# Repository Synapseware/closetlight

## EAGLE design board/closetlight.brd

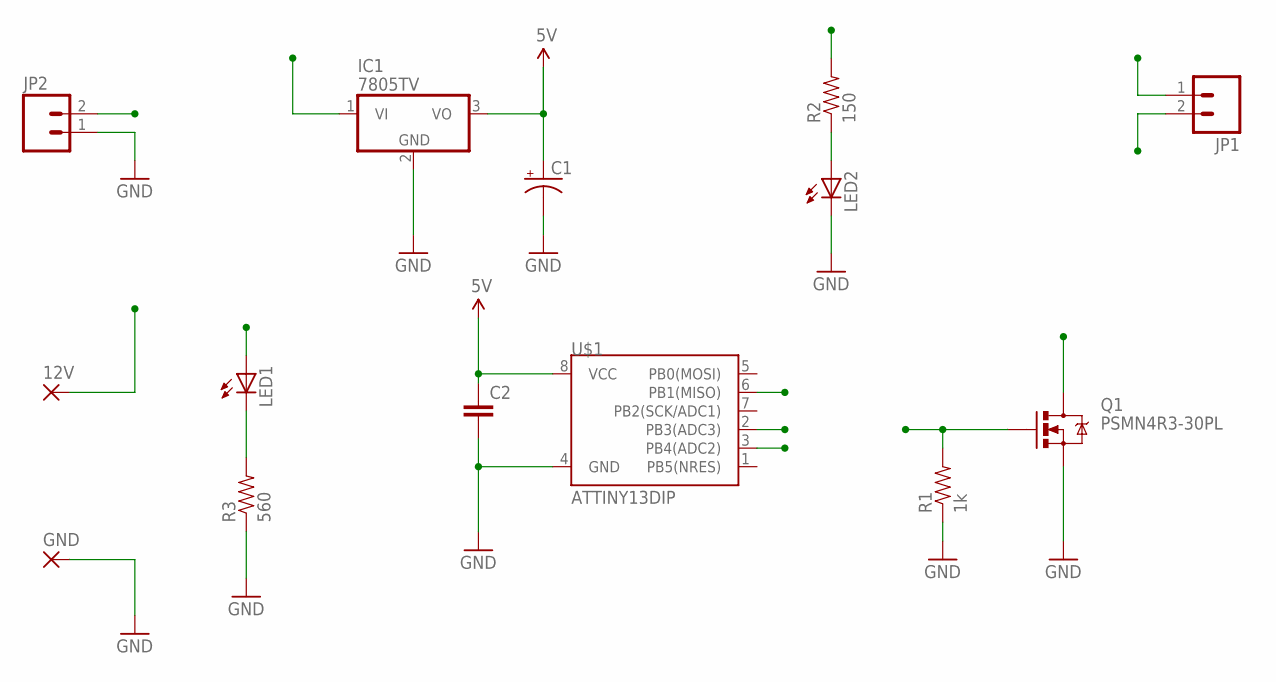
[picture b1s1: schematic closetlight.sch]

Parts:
12V: WIREPAD2,54/0,8; 2,54/0,8
C1: CAP_POLPTH2; CPOL-RADIAL-10UF-25V
C2: CAPEZ; CAP-PTH-SMALLEZ
GND: WIREPAD2,54/0,8; 2,54/0,8
IC1: 7805TV; TO220V
JP1, JP2: M02SPRING-2.54-RA; SPRINGTERMINAL-2.54MM-2
LED1, LED2: LED3MM
Q1: PSMN4R3-30PL; TO220V
R1: 1k; AXIAL-0.3
R2: 150; AXIAL-0.3
R3: 560; AXIAL-0.3
U$1: ATTINY13DIP; DIP08

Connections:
5V: C1.1 (+), C2.1, IC1.3 (VO), U$1.8 (VCC)
12V: 12V.1, IC1.1 (VI), JP1.2, LED1.A
DOOR_SW: JP2.2, U$1.2 (PB3(ADC3))
GND: C1.2 (-), C2.2, GND.1, IC1.2 (GND), JP2.1, LED2.K (C), Q1.3 (S), R1.P$1 (1), R3.P$1 (1), U$1.4 (GND)
LED_GND: JP1.1, Q1.2 (D)
unnamed: LED1.K (C), R3.P$2 (2)
unnamed: LED2.A, R2.P$1 (1)
PWM: Q1.1 (G), R1.P$2 (2), U$1.6 (PB1(MISO))
STATUS_LED: R2.P$2 (2), U$1.3 (PB4(ADC2))

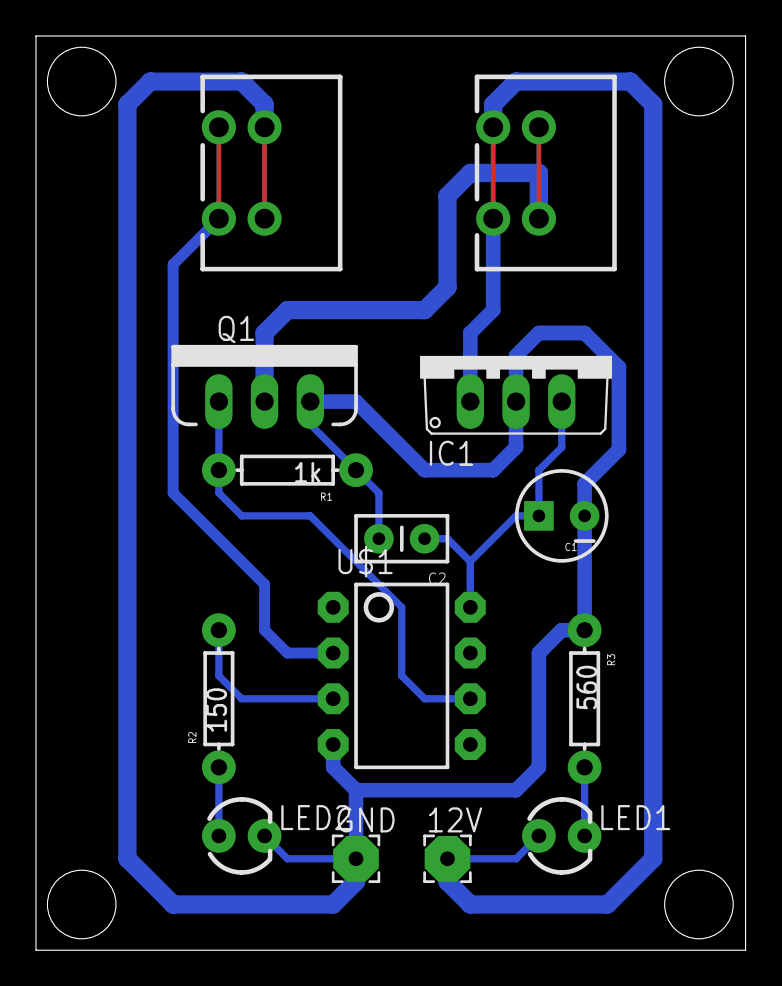
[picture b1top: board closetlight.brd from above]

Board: 2 copper layers, 39.4 x 50.8 mm, 14 parts (0 on the bottom side), 9 nets.

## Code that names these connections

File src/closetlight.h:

#ifndef __CLOSETLIGHT__H_
#define __CLOSETLIGHT__H_


#include <avr/io.h>
#include <avr/interrupt.h>
#include <avr/sleep.h>
#include <avr/pgmspace.h>
#include <avr/power.h>
#include <avr/wdt.h>
#include <math.h>


#define DOOR_PIN		PB3
#define PWM_OUT			PB1
#define STATUS_LED		PB4

#define PWM_LIMIT		200
#define CLK_DIV			1

const uint8_t			PWM_RANGE		= PWM_LIMIT - 1;		// steps in PWM window
const uint8_t			MAX_PWM			= PWM_LIMIT - 1;

const uint8_t			FADE_STEP_MS	= 10;					// wait Xms between fade changes
const uint8_t			FADE_STEPS		= 2;

const uint8_t			TICKS_MS		= (F_CPU / CLK_DIV / PWM_LIMIT / 1000);	// should be 48
const uint16_t			TICKS_S			= (F_CPU / CLK_DIV / PWM_LIMIT);


#define					EFFECT_OFF		0
#define					EFFECT_NORMAL	1
#define					EFFECT_DIMMED	2
#define					EFFECT_LOW		3
#define					EFFECT_BLINK	4
#define					EFFECT_SLEEPY	5

#define					BRIGHT_NORMAL	220
#define					BRIGHT_MED		80
#define					BRIGHT_LOW		30
#define					BRIGHT_OFF		0


const uint16_t			ONTIME_NORMAL	= 120;
const uint16_t			ONTIME_DIMMED	= 120;
const uint16_t			ONTIME_LOW		= 120;
const uint16_t			ONTIME_BLINK	= 300;
const uint16_t			ONTIME_SLEEPY	= 600;


const static uint8_t FADE_TABLE[] PROGMEM = {
	0,
	0 /*,
	0,
	0,
	0,
	1,
	1,
	1,
	1,
	1,
	1,
	1,
	1,
	1,
	1,
	1,
	1,
	1,
	2,
	2,
	2,
	2,
	2,
	2,
	2,
	3,
	3,
	3,
	3,
	4,
	4,
	4,
	5,
	5,
	5,
	6,
	6,
	7,
	8,
	8,
	9,
	10,
	10,
	11,
	12,
	13,
	14,
	15,
	17,
	18,
	20,
	21,
	23,
	25,
	27,
	29,
	32,
	34,
	37,
	40,
	44,
	47,
	51,
	56,
	60,
	65,
	71,
	77,
	83,
	90,
	97,
	105,
	114,
	124,
	134,
	145,
	157,
	170,
	185,
	200
	*/
};
const static uint8_t FADE_TABLE_LEN = sizeof(FADE_TABLE)/sizeof(uint8_t);




#endif

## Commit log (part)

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2014-11-03 Updating closet light behavior so it has timeouts and effects if left open for too long

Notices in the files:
parts and their libraries:
SparkFun-DigitalIC: Licensing: CC v3.0 Share-Alike You are welcome to use this library for commercial purposes.
